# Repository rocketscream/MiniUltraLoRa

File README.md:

# Mini Ultra LoRa

Mini Ultra LoRa is an Arduino compatible ATmega4808 board that is suitable for ultra low power wireless applications. During deep sleep mode, the board consumes only 5 uA (with the on-board radio module in sleep mode) when powered by a 3.6 V source. The board comes equipped with a 2Kb I2C serial EEPROM with pre-programmed EUI-64™ MAC ID 24AA025E64T chip to be used as DEVEUI in a LoRaWAN network and E19-900M20S2 LoRa radio module. Option to use various battery type, cell combination and chemistry such as 2xAA or 3xAA (alkaline, NiMH), CR123A, LiFeFO4, and Li-Ion/Pol. No charger IC is included on-board.

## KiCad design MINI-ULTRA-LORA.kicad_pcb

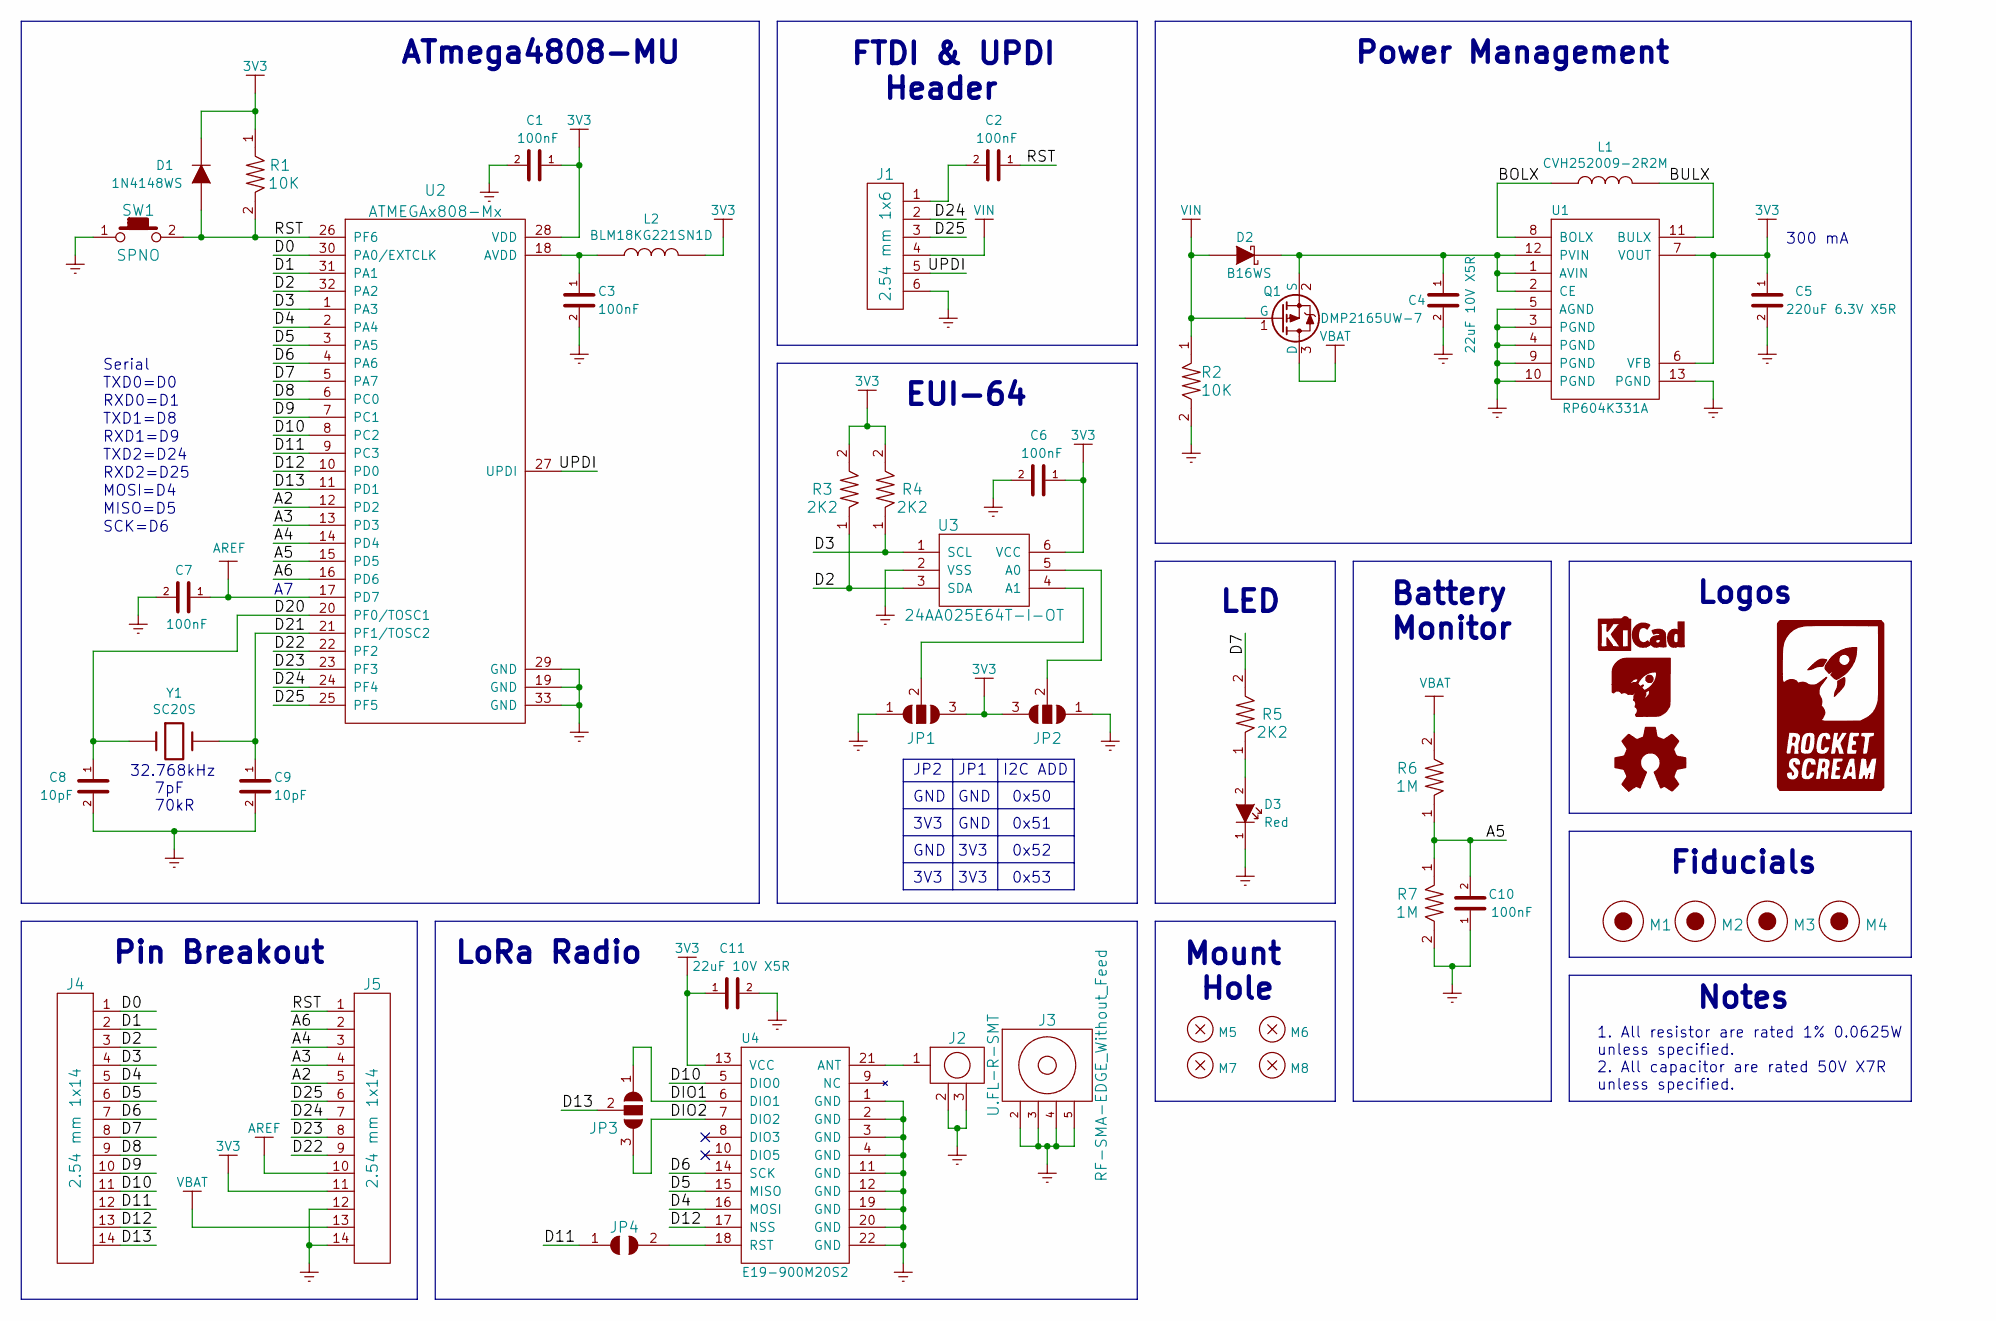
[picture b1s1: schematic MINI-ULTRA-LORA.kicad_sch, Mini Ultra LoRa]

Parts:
C1, C2, C3, C6, C7, C10: 100nF; C_0603
C4, C11: 22uF 10V X5R; C_0603
C5: 220uF 6.3V X5R; C_1206
C8, C9: 10pF; C_0603
D1: 1N4148WS; SOD-323
D2: B16WS; SOD-323
D3: Red; LED_0603
J1: 2.54 mm 1x6; HDR_1x6_Pitch2.54mm
J2: U.FL-R-SMT
J3: RF-SMA-EDGE_Without_Feed
J4, J5: 2.54 mm 1x14; HDR_1x14_Pitch2.54mm
JP1, JP2, JP3: JUMPER-2-WAY; JUMPER-2-WAY-SMD
JP4: JUMPER-1-WAY; JUMPER-1-WAY-SMD
L1: CVH252009-2R2M; I_2520
L2: BLM18KG221SN1D; I_0603
LOGO1: LOGO-KICAD; LOGO-KICAD_XXXSmall
LOGO2: LOGO-ROCKET-SCREAM-WITHOUT-TEXT; LOGO-ROCKET-SCREAM_Without_Text_XXXXSmall
LOGO3: LOGO-ROCKET-SCREAM-VERTICAL; LOGO-ROCKET-SCREAM_Vertical_XSmall
LOGO4: LOGO-OSHW; LOGO-OSHW_XXSmall
M1, M2, M3, M4: FIDUCIAL; FIDUCIAL-0.5MM_CROSS
M5, M6, M7, M8: MOUNT_HOLE; HOLE_NPTH_2.2MM
Q1: DMP2165UW-7; SOT-323
R1, R2: 10K; R_0603
R3, R4, R5: 2K2; R_0603
R6, R7: 1M; R_0603
SW1: SPNO; TS-1086E-12
U1: RP604K331A; DFN-12
U2: ATMEGAx808-Mx; QFN-32_5x5mm_Pitch0.5mm
U3: 24AA025E64T-I-OT; SOT-23-6
U4: E19-900M20S2
Y1: SC20S; SC-20S

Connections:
3V3: C1.1, C5.1, C6.1, C11.1, D1.1 (K), J5.11, JP1.3, JP2.3, L2.2, R1.1, R3.2, R4.2, U1.6 (VFB), U1.7 (VOUT), U2.28 (VDD), U3.6 (VCC), U4.13 (VCC)
/A2: J5.5, U2.12 (PD2)
/A3: J5.4, U2.13 (PD3)
/A4: J5.3, U2.14 (PD4)
/A5: C10.2, R6.1, R7.1, U2.15 (PD5)
/A6: J5.2, U2.16 (PD6)
/BOLX: L1.1, U1.8 (BOLX)
/BULX: L1.2, U1.11 (BULX)
/D0: J4.1, U2.30 (PA0/EXTCLK)
/D1: J4.2, U2.31 (PA1)
/D2: J4.3, R3.1, U2.32 (PA2), U3.3 (SDA)
/D3: J4.4, R4.1, U2.1 (PA3), U3.1 (SCL)
/D4: J4.5, U2.2 (PA4), U4.16 (MOSI)
/D5: J4.6, U2.3 (PA5), U4.15 (MISO)
/D6: J4.7, U2.4 (PA6), U4.14 (SCK)
/D7: J4.8, R5.2, U2.5 (PA7)
/D8: J4.9, U2.6 (PC0)
/D9: J4.10, U2.7 (PC1)
/D10: J4.11, U2.8 (PC2), U4.5 (DIO0)
/D11: J4.12, JP4.1, U2.9 (PC3)
/D12: J4.13, U2.10 (PD0), U4.17 (NSS)
/D13: J4.14, JP3.2, U2.11 (PD1)
/D20: C8.1, U2.20 (PF0/TOSC1), Y1.1
/D21: C9.1, U2.21 (PF1/TOSC2), Y1.2
/D22: J5.9, U2.22 (PF2)
/D23: J5.8, U2.23 (PF3)
/D24: J1.2, J5.7, U2.24 (PF4)
/D25: J1.3, J5.6, U2.25 (PF5)
/DIO1: JP3.1, U4.6 (DIO1)
/DIO2: JP3.3, U4.7 (DIO2)
/RST: C2.1, D1.2 (A), J5.1, R1.2, SW1.2, U2.26 (PF6)
/UPDI: J1.5, U2.27 (UPDI)
AREF: C7.1, J5.10, U2.17 (PD7)
GND: C1.2, C3.2, C4.2, C5.2, C6.2, C7.2, C8.2, C9.2, C10.1, C11.2, D3.1 (K), J1.6, J2.2, J2.3, J3.2, J3.3, J3.4, J3.5, J5.12, J5.14, JP1.1, JP2.1, R2.2, R7.2, SW1.1, U1.3 (PGND), U1.4 (PGND), U1.5 (AGND), U1.9 (PGND), U1.10 (PGND), U1.13 (PGND), U2.19 (GND), U2.29 (GND), U2.33 (GND), U3.2 (VSS), U4.1 (GND), U4.2 (GND), U4.3 (GND), U4.4 (GND), U4.11 (GND), U4.12 (GND), U4.19 (GND), U4.20 (GND), U4.22 (GND)
unnamed: C2.2, J1.1
unnamed: C3.1, L2.1, U2.18 (AVDD)
unnamed: C4.1, D2.1 (K), Q1.2 (S), U1.1 (AVIN), U1.2 (CE), U1.12 (PVIN)
unnamed: D3.2 (A), R5.1
unnamed: J2.1, U4.21 (ANT)
unnamed: JP1.2, U3.4 (A1)
unnamed: JP2.2, U3.5 (A0)
unnamed: JP4.2, U4.18 (RST)
VBAT: J5.13, Q1.3 (D), R6.2
VIN: D2.2 (A), J1.4, Q1.1 (G), R2.1

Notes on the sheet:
Notes
Logos
3V3
FTDI & UPDI Header
GND
0x52
Serial
TXD0=D0
MOSI=D4
300 mA
TXD2=D24
RXD0=D1
EUI-64
1. All resistor are rated 1% 0.0625W unless specified. 2. All capacitor are rated 50V X7R unless specified.
ATmega4808-MU
MISO=D5
Power Management
JP2
LED
Mount Hole
SCK=D6
Battery Monitor
Pin Breakout
RXD1=D9
32.768kHz 7pF 70kR
Fiducials
I2C ADD
RXD2=D25
LoRa Radio
0x53
0x51
0x50
JP1
TXD1=D8

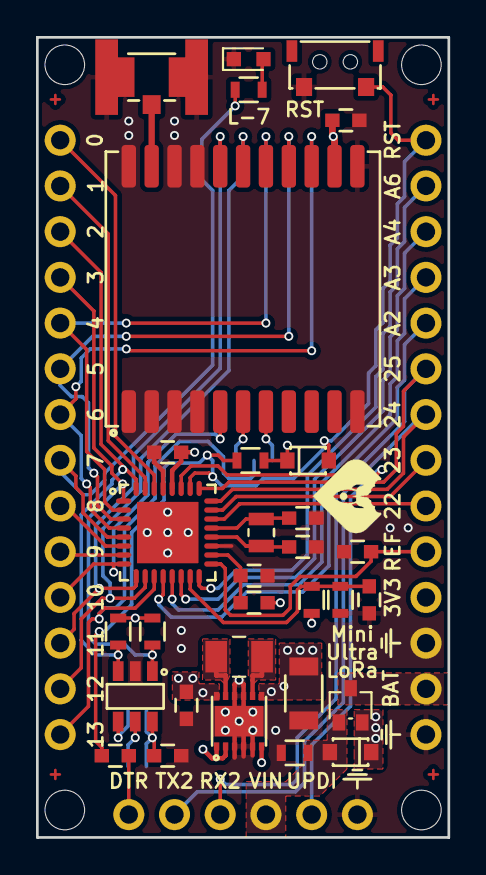
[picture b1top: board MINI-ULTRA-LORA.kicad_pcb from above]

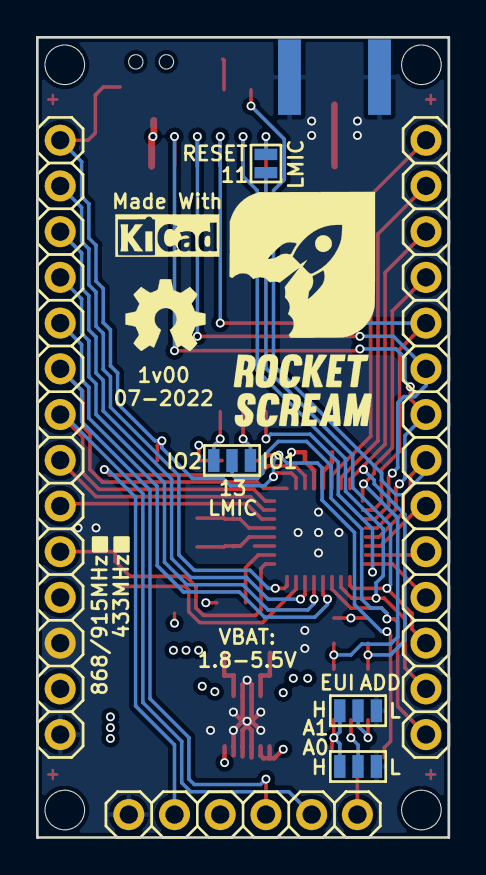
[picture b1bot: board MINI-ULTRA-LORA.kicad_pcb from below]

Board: 4 copper layers, 22.9 x 44.4 mm, 51 parts (10 on the bottom side), 44 nets.

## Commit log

2022-08-31 v1.00
